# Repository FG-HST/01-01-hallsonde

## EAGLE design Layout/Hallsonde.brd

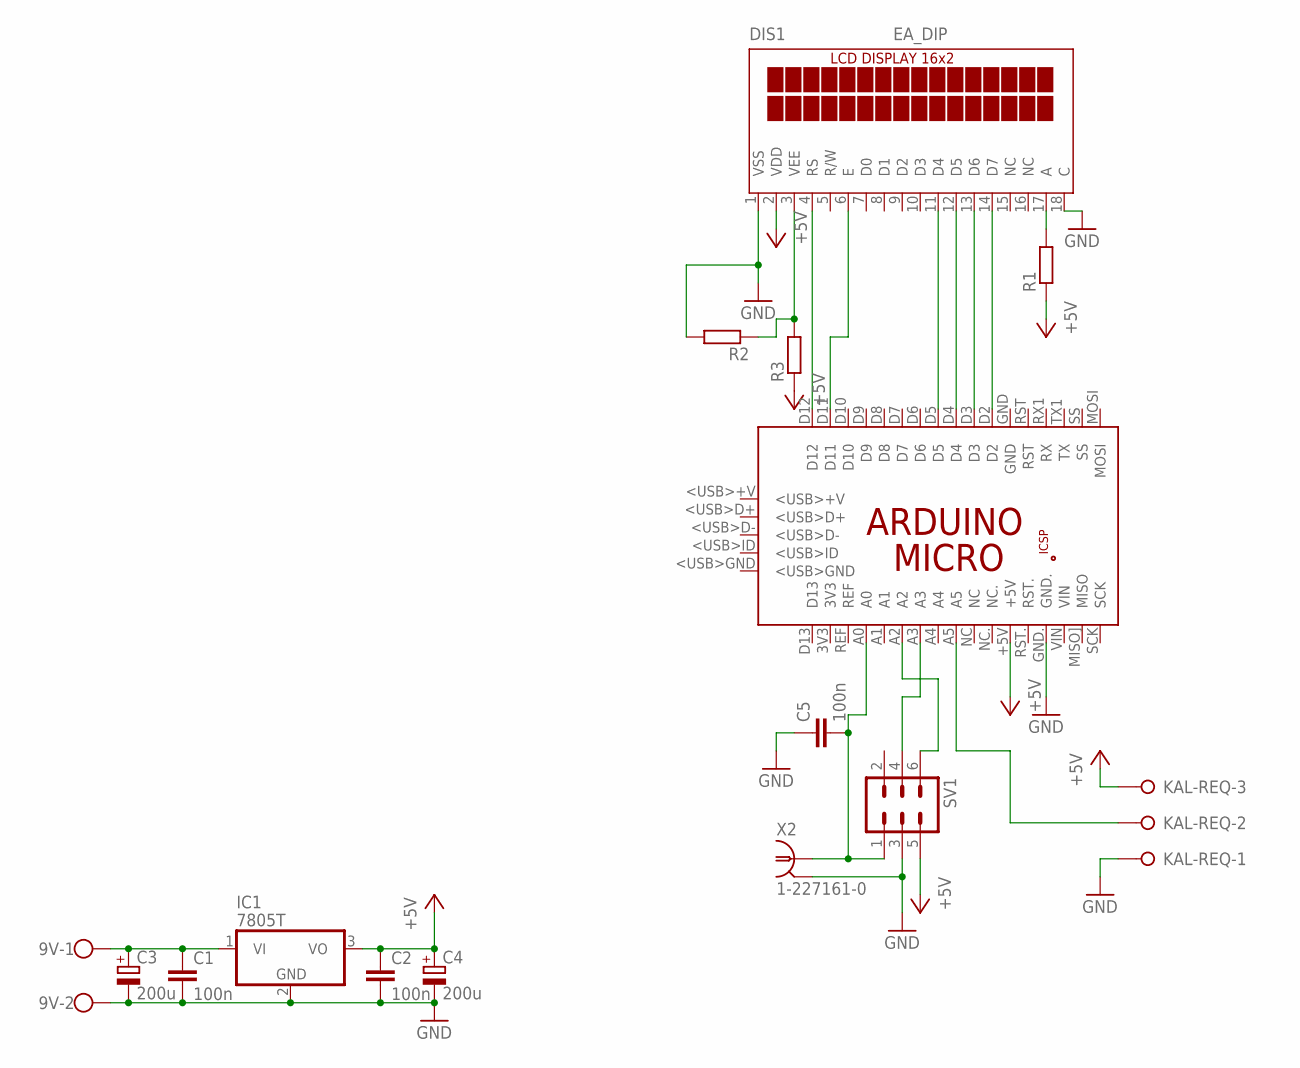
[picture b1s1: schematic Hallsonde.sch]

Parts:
9V: W237-102
C1, C2, C5: 100n; C0805
C3, C4: 200u; E2,5-6E
DIS1: EA_DIP
IC1: 7805T; TO220H
KAL-REQ: W237-3E
PCB1: ARDUINO_MICRO
R1, R2, R3: R-EU_M0805; M0805
SV1: ML6L
X2: 1-227161-0; AMP_227161

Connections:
+5V: C2.1, C4.+, DIS1.2 (VDD), IC1.3 (VO), KAL-REQ.3, PCB1.+5V, R1.1, R3.1, SV1.5
GND: 9V.2, C1.2, C2.2, C3.-, C4.-, C5.1, DIS1.1 (VSS), DIS1.18 (C), IC1.2 (GND), KAL-REQ.1, PCB1.GND., R2.2, SV1.3, X2.2
unnamed: 9V.1, C1.1, C3.+, IC1.1 (VI)
unnamed: DIS1.4 (RS), PCB1.D12
unnamed: DIS1.6 (E), PCB1.D11
unnamed: DIS1.11 (D4), PCB1.D5
unnamed: DIS1.12 (D5), PCB1.D4
unnamed: DIS1.13 (D6), PCB1.D3
unnamed: DIS1.14 (D7), PCB1.D2
unnamed: DIS1.17 (A), R1.2
unnamed: C5.2, PCB1.A0, SV1.1, X2.1
unnamed: PCB1.A3, SV1.4
unnamed: PCB1.A2, SV1.6
unnamed: KAL-REQ.2, PCB1.A5
unnamed: DIS1.3 (VEE), R2.1, R3.2

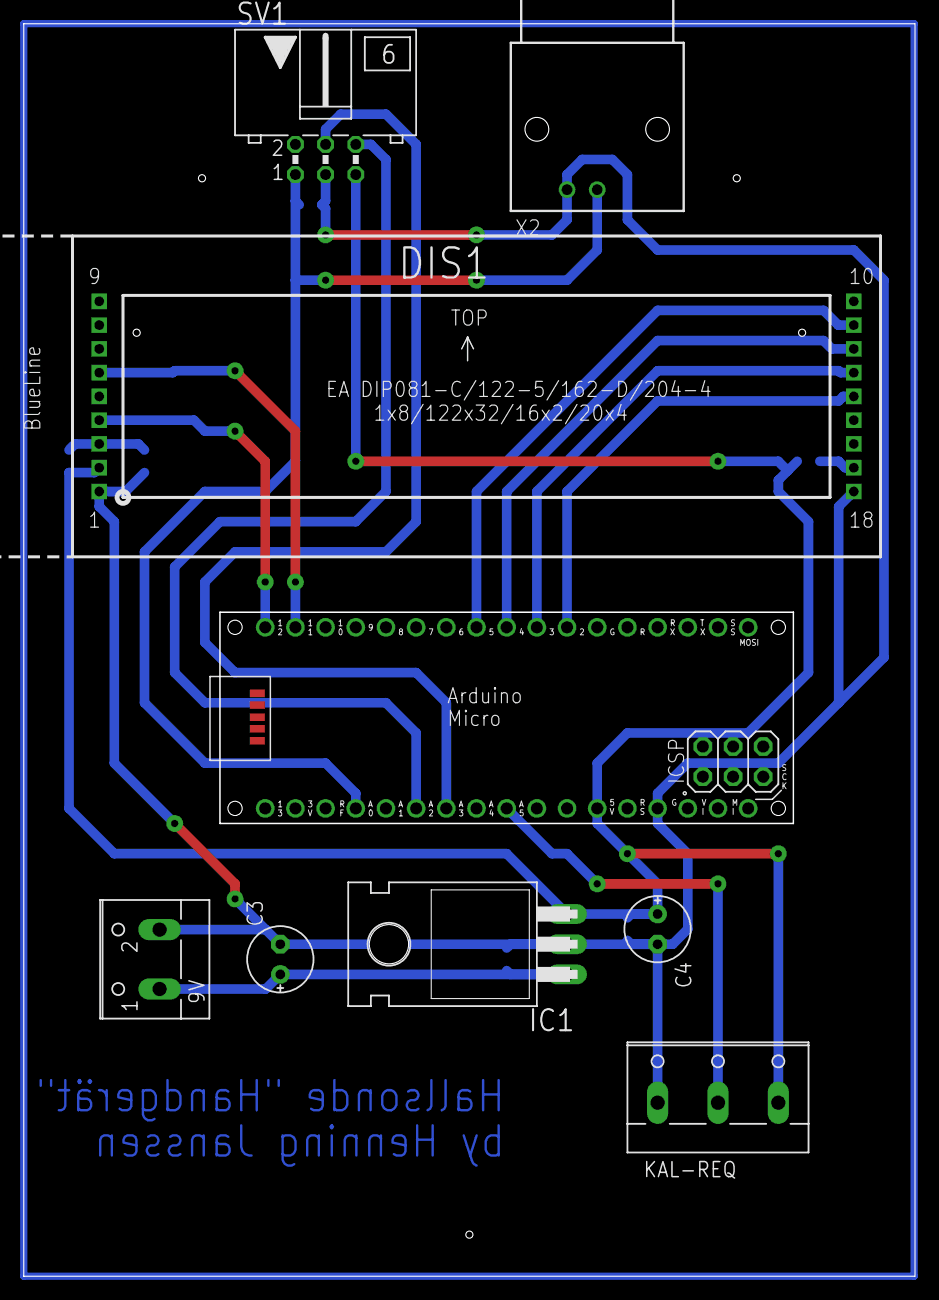
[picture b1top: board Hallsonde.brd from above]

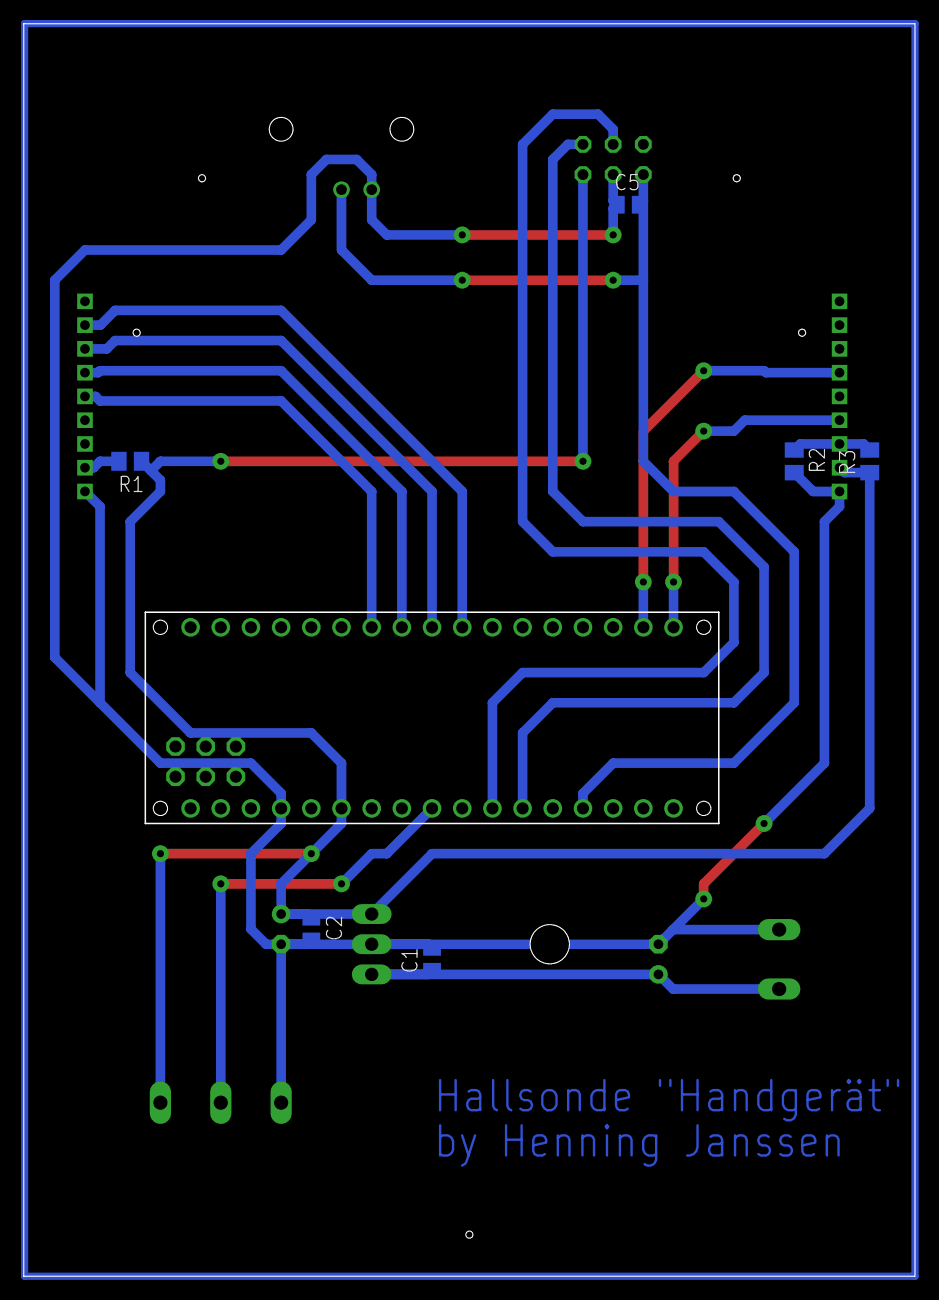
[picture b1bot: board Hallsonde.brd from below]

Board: 2 copper layers, 74.9 x 105.3 mm, 15 parts (6 on the bottom side), 15 nets.

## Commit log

2016-01-20 add Code, Layout
2016-01-22 final commit
    the final commit with documentation and pictures
